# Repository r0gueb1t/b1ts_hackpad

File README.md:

# b1ts-hackpad

<h3><b>CAD:</b></h3><br>

<h3><b>Schematic:</b></h3><br>

<h3><b>PCB:</b></h3><br>

<h3><b>Case:</b></h3><br>

I haven't made a PROPER case for my project, because I love to show off the insides of my gadgets. Raw, unfiltered, exposed. However, I have added a baseplate as per the suggestion of <a href="https://github.com/nimitvijayvargee">nimit</a> from Blueprint.

<h3><b>BOM:</b></h3>
Here's what I used for the device:
<ul>
  <li>1x XIAO_RP2040 module</li>
  <li>4x Cherry MX Switches</li>
  <li>4x DSA Keycaps</li>
  <li>1x EC11 Rotary Encoder</li>
  <li>2x SK6812 Mini LEDs</li>
  <li>4x M3x16mm screws</li>
  <li>4x M3x5mmx4mm inserts</li>
</ul>

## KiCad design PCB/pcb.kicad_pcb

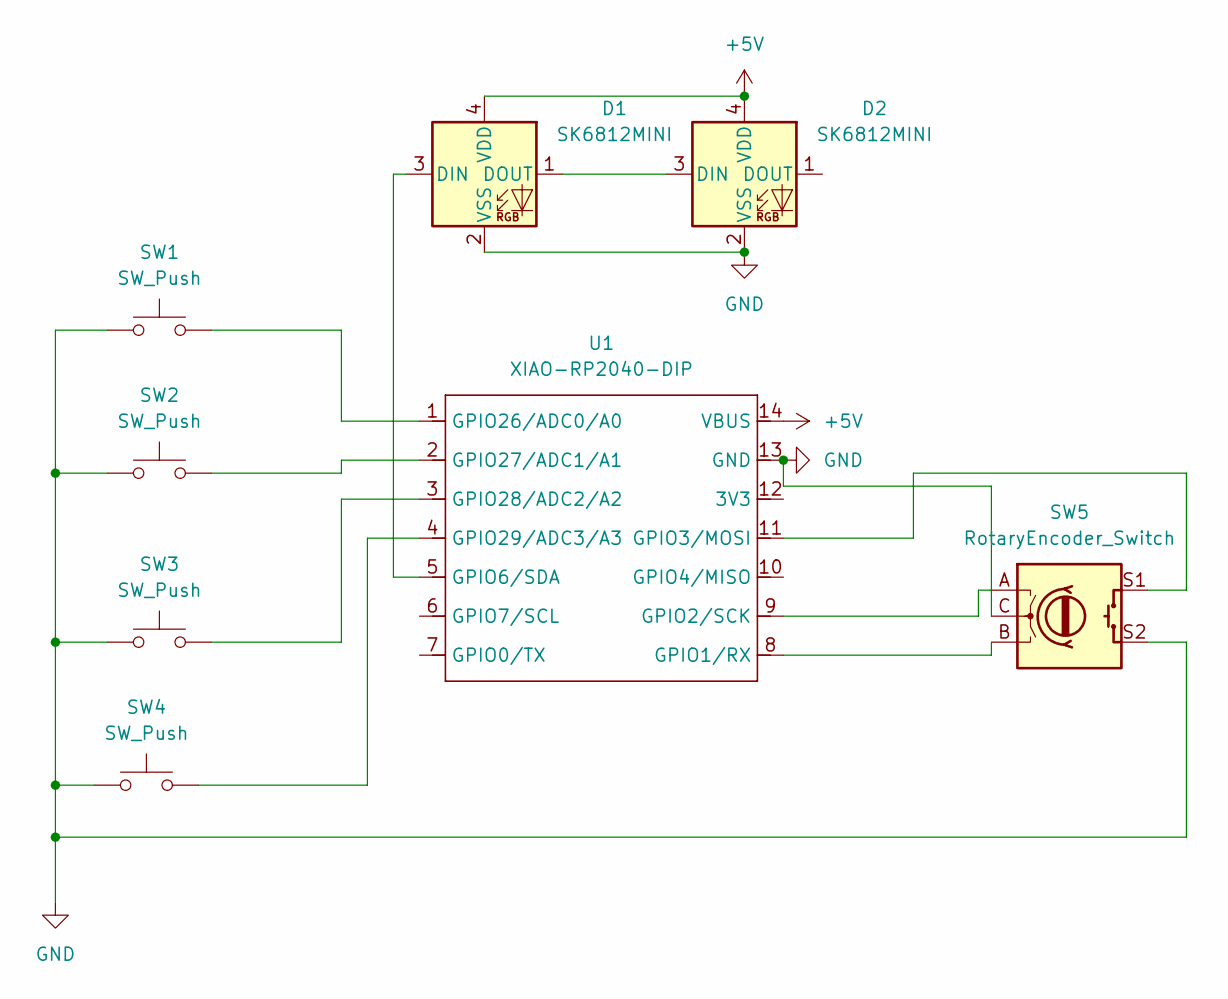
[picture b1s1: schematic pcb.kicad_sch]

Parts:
D1, D2: SK6812MINI; LED_SK6812MINI_PLCC4_3.5x3.5mm_P1.75mm
SW1, SW2, SW3, SW4: SW_Push; SW_Cherry_MX_1.00u_PCB
SW5: RotaryEncoder_Switch; RotaryEncoder_Alps_EC11E-Switch_Vertical_H20mm
U1: XIAO-RP2040-DIP

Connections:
+5V: D1.4 (VDD), D2.4 (VDD), U1.14 (VBUS)
GND: D1.2 (VSS), D2.2 (VSS), SW1.1, SW2.1, SW3.1, SW4.1, SW5.C, SW5.S2, U1.13 (GND)
unnamed: D1.3 (DIN), U1.5 (GPIO6/SDA)
unnamed: D1.1 (DOUT), D2.3 (DIN)
unnamed: SW5.B, U1.8 (GPIO1/RX)
unnamed: SW5.A, U1.9 (GPIO2/SCK)
unnamed: SW5.S1, U1.11 (GPIO3/MOSI)
unnamed: SW1.2, U1.1 (GPIO26/ADC0/A0)
unnamed: SW2.2, U1.2 (GPIO27/ADC1/A1)
unnamed: SW3.2, U1.3 (GPIO28/ADC2/A2)
unnamed: SW4.2, U1.4 (GPIO29/ADC3/A3)

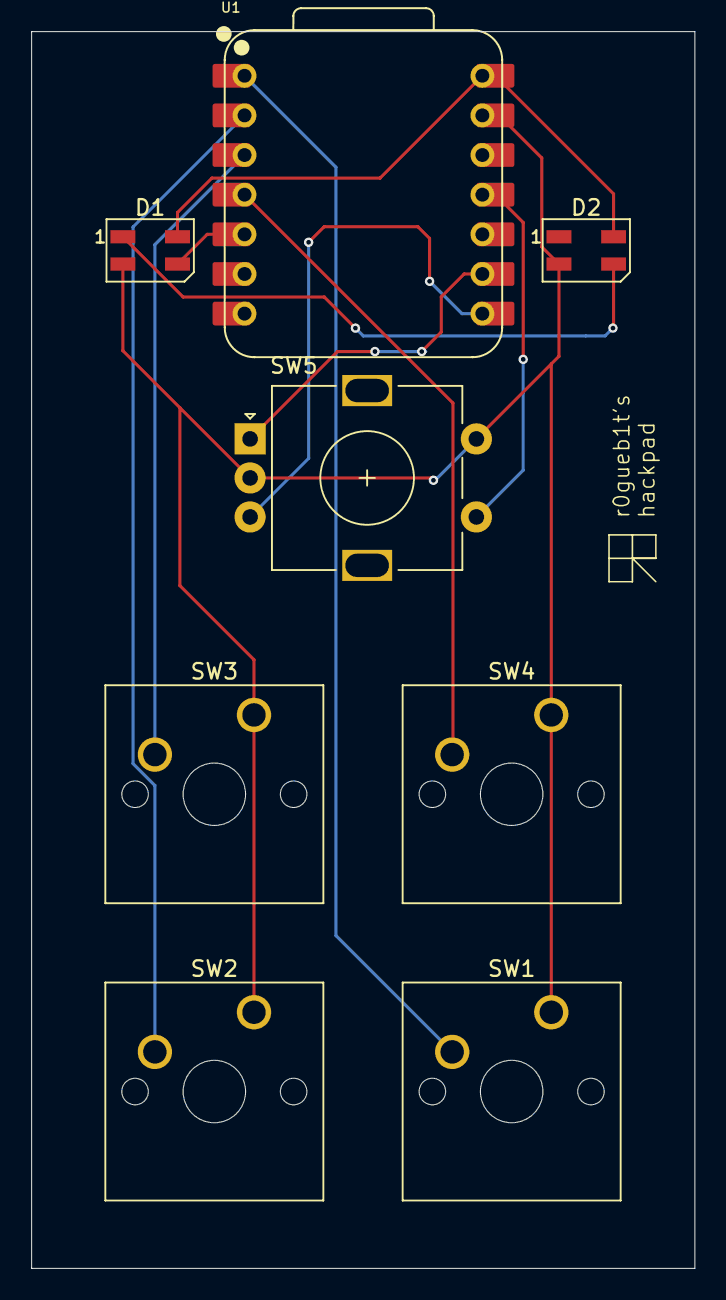
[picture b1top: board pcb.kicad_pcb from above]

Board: 2 copper layers, 42.5 x 79.2 mm, 8 parts (0 on the bottom side), 11 nets.

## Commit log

2025-12-09 Initial commit with Git
2025-12-09 Draft push
2025-12-11 Update README.md
    Fixed typo
